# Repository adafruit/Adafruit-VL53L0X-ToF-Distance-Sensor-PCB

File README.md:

# PCB files for the Adafruit VL53L0X ToF Distance Sensor

<a href="http://www.adafruit.com/products/3317"><br/></a>
<a href="http://www.adafruit.com/products/3317"><br/>Click here to purchase one from the Adafruit shop</a>

__Format is EagleCAD schematic and board layout__

The __VL53L0X__ is a *Time of Flight* distance sensor like no other you've used! The sensor contains a very tiny invisible laser source, and a matching sensor. The VL53L0X can detect the "time of flight", or how long the light has taken to bounce back to the sensor. Since it uses a very narrow light source, it is good for determining distance of only the surface directly in front of it. Unlike sonars that bounce ultrasonic waves, the 'cone' of sensing is very narrow. Unlike IR distance sensors that try to measure the amount of light bounced, the VL53L0x is much more precise and doesn't have linearity problems or 'double imaging' where you can't tell if an object is very far or very close.

This is the 'big sister' of the [VL6180X ToF sensor](https://www.adafruit.com/products/3316), and can handle about 50mm to 1200mm of range distance. If you need a smaller/closer range, check out the VL6180X which can measure 5mm to 200mm and also contains a light sensor.

The sensor is small and easy to use in any robotics or interactive project. Since it needs 2.8V power and logic we put the little fellow on a breakout board with a regulator and level shifting. You can use it with any 3-5V power or logic microcontroller with no worries. Each order comes with a small piece of header. Solder the header onto your breakout board with your iron and some solder and wire it up for instant distance-sensing-success!

Communicating to the sensor is done over I2C with an API written by ST, so its not too hard to port it to your favorite microcontroller. We've written a wrapper library for Arduino so you can use it with any of your Arduino-compatible boards.

[Check out our tutorial for code, schematics, diagrams and more!](https://learn.adafruit.com/adafruit-vl53l0x-micro-lidar-distance-sensor-breakout)

## License

Adafruit invests time and resources providing this open source design, 
please support Adafruit and open-source hardware by purchasing 
products from Adafruit!

Designed by Adafruit Industries.  
Creative Commons Attribution, Share-Alike license, check license.txt for more information
All text above must be included in any redistribution

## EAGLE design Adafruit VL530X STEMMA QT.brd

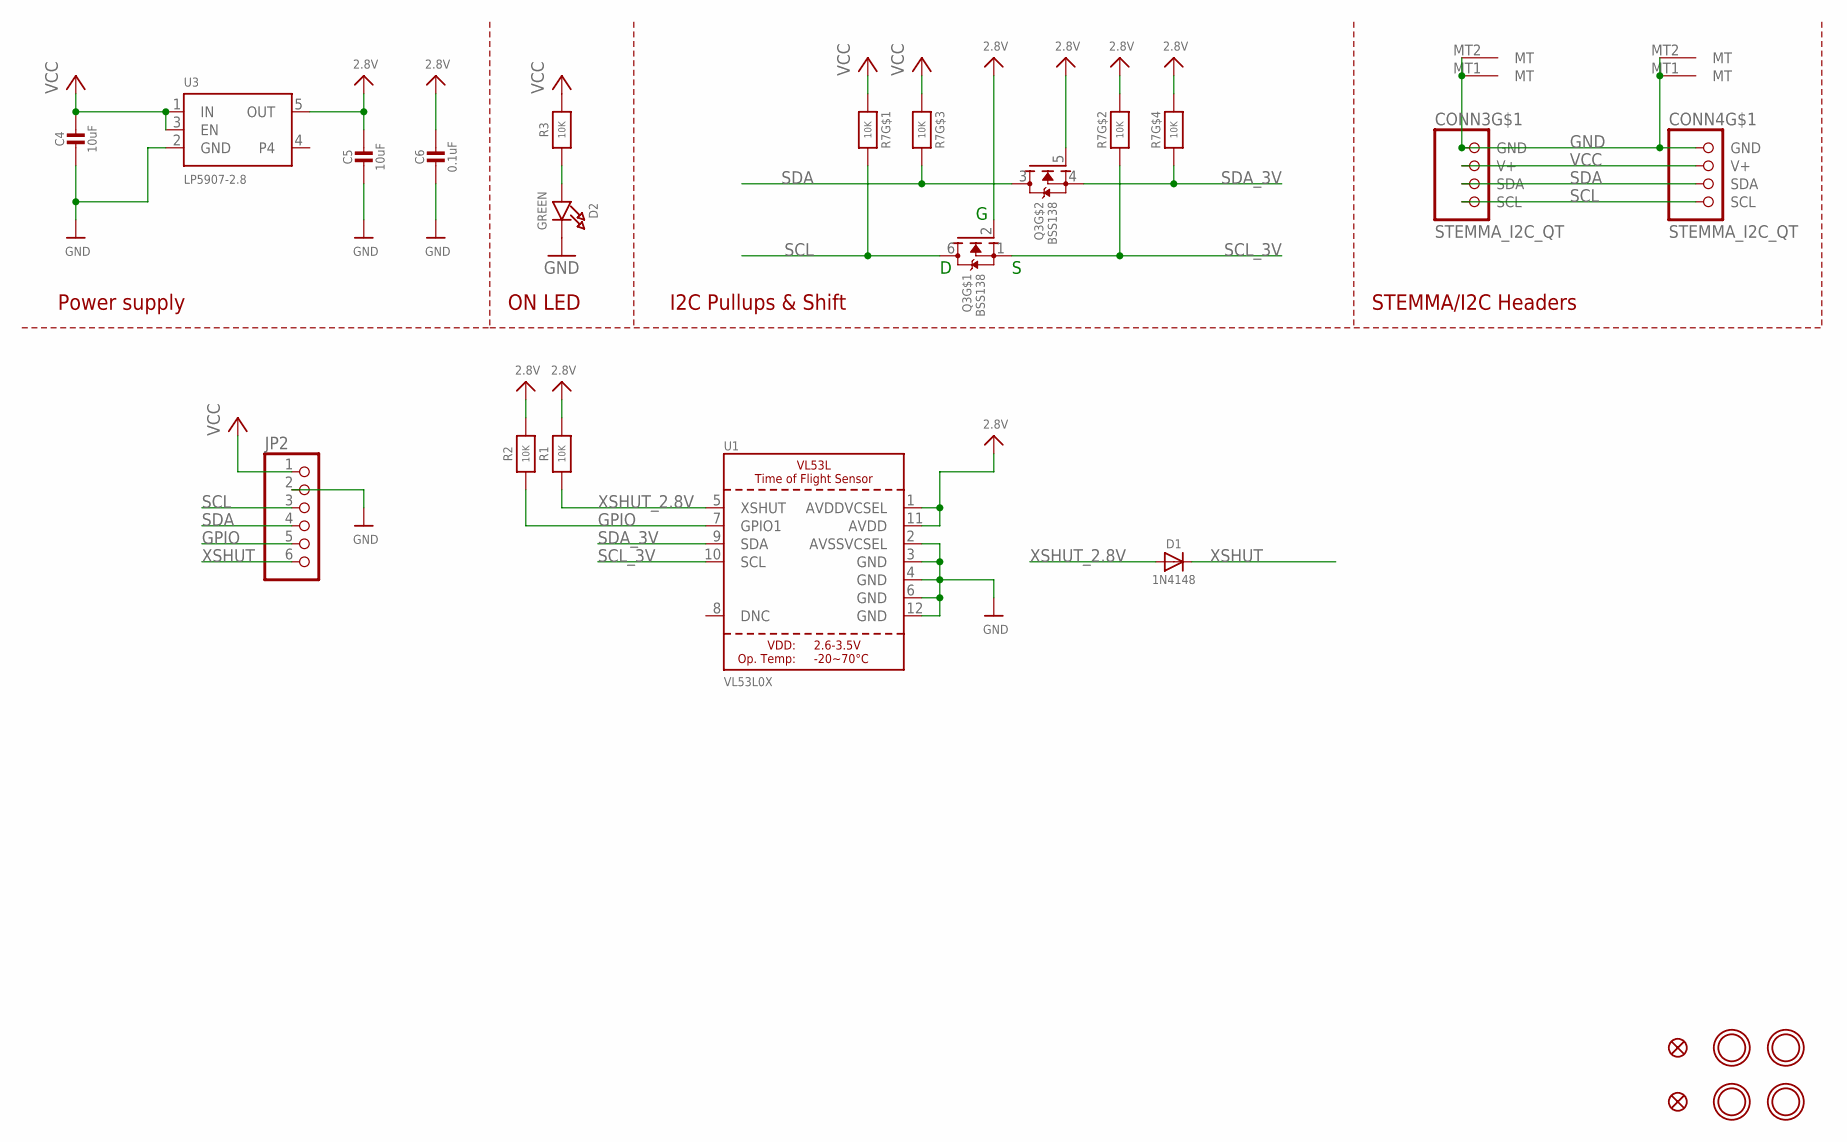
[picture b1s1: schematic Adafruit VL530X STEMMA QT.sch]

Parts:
C4, C5: 10uF; 0805-NO
C6: 0.1uF; 0603-NO
CONN3, CONN4: STEMMA_I2C_QT; JST_SH4
D1: 1N4148; SOD-323
D2: GREEN; CHIPLED_0603_NOOUTLINE
FID1, FID4: FIDUCIAL_1MM
JP2: HEADER-1X670MIL; 1X06_ROUND_70
Q3: BSS138; SOT363
R1, R2, R3: 10K; 0603-NO
R7: 10K; RESPACK_4X0603
U1: VL53L0X; LGA12_ST
U3: LP5907-2.8; SOT23-5
U$30, U$31, U$33, U$34: MOUNTINGHOLE2.5; MOUNTINGHOLE_2.5_PLATED

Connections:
2.8V: C5.1, C6.1, Q3.2 (G), Q3.5 (G), R1.2, R2.2, R7.2 (1), R7.4 (1), U1.1 (AVDDVCSEL), U1.11 (AVDD), U3.5 (OUT)
GND: C4.2, C5.2, C6.2, CONN3.1 (GND), CONN3.MT1 (MT), CONN3.MT2 (MT), CONN4.1 (GND), CONN4.MT1 (MT), CONN4.MT2 (MT), D2.C, JP2.2, U1.2 (AVSSVCSEL), U1.3 (GND), U1.4 (GND), U1.6 (GND), U1.12 (GND), U3.2 (GND)
GPIO: JP2.5, R2.1, U1.7 (GPIO1)
unnamed: D2.A, R3.1
SCL: CONN3.4 (SCL), CONN4.4 (SCL), JP2.3, Q3.6 (D), R7.8 (2)
SCL_3V: Q3.1 (S), R7.7 (2), U1.10 (SCL)
SDA: CONN3.3 (SDA), CONN4.3 (SDA), JP2.4, Q3.3 (D), R7.6 (2)
SDA_3V: Q3.4 (S), R7.5 (2), U1.9 (SDA)
VCC: C4.1, CONN3.2 (V+), CONN4.2 (V+), JP2.1, R3.2, R7.1, R7.3 (1), U3.1 (IN), U3.3 (EN)
XSHUT: D1.C, JP2.6
XSHUT_2.8V: D1.A, R1.1, U1.5 (XSHUT)

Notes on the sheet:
I2C Pullups & Shift
STEMMA/I2C Headers
ON LED
Power supply

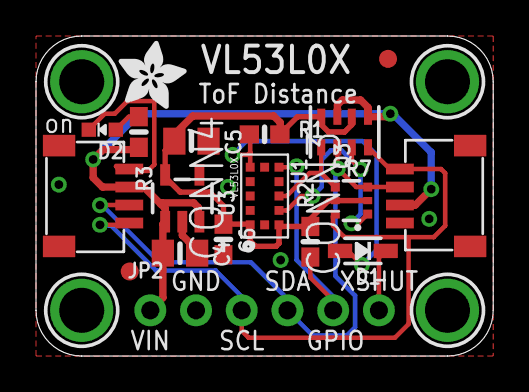
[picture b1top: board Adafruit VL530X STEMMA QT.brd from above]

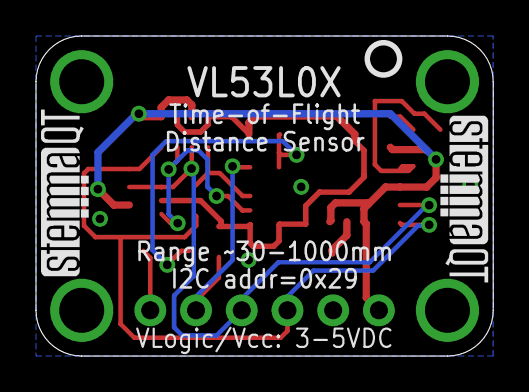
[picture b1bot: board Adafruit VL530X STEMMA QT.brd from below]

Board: 2 copper layers, 25.4 x 17.8 mm, 25 parts (3 on the bottom side), 11 nets.

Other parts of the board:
U$36: ADAFRUIT_3.5MM
U$37: PCBFEAT-REV-040
U$38, U$39: STEMMAQT

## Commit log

2016-11-23 inity
2019-04-10 Update the product page reference
    to patch https://github.com/adafruit/Adafruit-VL53L0X-ToF-Distance-Sensor-PCB/issues/2
2019-05-15 image + readme + license
2020-07-24 Add STEMMA QT board files.
2020-07-24 Add STEMMA QT version image.

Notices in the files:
parts and their libraries:
microbuilder: This work is placed in the public domain, and may be freely used for commercial and non-commercial work with the following conditions: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
